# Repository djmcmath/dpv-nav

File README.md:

Tern

Built for Exploration

Welcome to Tern: underwater navigation for technical divers who are tired of getting lost and wondering where they went.

Nominally, this is a simple dead reckoning navigation system designed to be installed on DPVs (aka "scooters").  I'm making this source-available, and attempting to use as many readily-available parts as possible to provide something that'll be accessible to most technical divers.  Some parts of the build are technical -- you'll need to manufacture and solder custom PCBs, flash firmware to ESP32s, and so on, but even if you can't solder or print parts, if you're in the technical diving community, odds are excellent you know someone who can.  

Yes, it's vibe coded.  I used Claude Code to great effect, covering a ton of ground in a matter of months that I hadn't been able to get through on my own.  Say what you will about AI-supported coding, this project exists, and wouldn't without AI support.

About the name:
- It's called Tern, after the Arctic Tern, which is just a fantastic bird.  They navigate from the north pole to the south every year -- mating in the Antarctic, then raising their young in transit and growing to maturity in the Arctic.  Then they migrate BACK to do it all again the next year.  Insane.
- But hey, if a tiny bird can navigate thousands of kilometers every year, perhaps we can build a DIY-capable device that'll allow divers to cover much smaller distances with confidence underwater.

Framing:
- This is NOT "underwater GPS."  GPS doesn't work underwater, and there's no magic that will allow us to violate the laws of physics.  Precise positioning underwater is a delightful engineering problem, and there are a variety of excellent ways to know exactly where you are.  Precision is a function of expense -- how precise your position is depends almost entirely on how much you're willing to spend to get there.
- This *is* a tool that'll tell you much more accurately where you are than anything else readily available in the space at this price point.  If your current process is to read your magnetic compass and keep track of time and distance using your dive computer and mental gymnastics, this will save you a lot of effort and produce a dramatically more accurate result.  I did a dive the other day where my buddy used her wrist-mounted compass -- showing plus or minus 20deg from what I was showing on the DPV -- and, coincidentally, we still hit the wreck.
- The formal name is "dead reckoning," using heading and speed (plus an initial position from GPS on the surface) to determine an "estimated position."  Accuracy of the final position depends on quality of calibration, accuracy of initial position, and time / distance since last fix.  Each iteration takes the previous estimated position, adds the current course and speed, and produces a new estimated position.  Errors, naturally, compound, so the longer it's been since you've actually known where you were, the farther off you may be from where it says you are.  Additionally, knowing EXACTLY where you start matters -- that's why there's external GPS and an indication of fix quality on the headline of the display.
- For planning purposes, assume that the error is about 10% of the distance since your last fix.  So if you submerge and run for 500m, assume you're within 50m of the target.  That'll require dropping a marker and running a reel out to conduct a search to find the wreck.  But at least you have some confidence that you're within a reasonable distance of the right spot.  If you calibrate with care and run a few tests on known courses, you may find that your accuracy is much better.  I've had runs with error rates in the 2-3%, for example.  (Future versions will track heading and speed calibration vs reality to estimate position uncertainty, and will allow reducing uncertainty by crossing known navigation points.)
- Safety note: It's an aid, not an authoritative answer.  Dive within your limits and your training.  Don't blindly follow the computer -- it doesn't know your certification limits or how much breathing gas you have or, frankly, anything about your dive plan.  Heck, it doesn't even know where you are -- it's just estimating.  Additionally, you're adding a device with cables to your DPV, so you're bringing entanglement risk and complexity to your already existing challenges.  So be careful.

Workflow and usage:
- Assemble the whole device
- Flash the firmware to both units (NAV and DISPLAY)
- On the first power-up, the unit will attempt to calibrate gyro and accelerometer.  There will be a series of prompts displayed in the serial monitor walking you through this process.  You should only need to do this once.  Getting it right is important, but it's the least important input to the AHRS algorithm.
- Set up wireless:
-- You can keep it as something that you connect to with a wireless device, or you can set it to automatically connect to a known wireless network.  Calibration is much easier if it has a good full-time wireless connection.
-- Make sure wireless is on ("WiFi AP" in white (or green), not gray, on the display)
-- Connect to wireless AP "Tern," with password "password", then browse to 192.168.4.1.
-- In the "WiFi Networks" section, press "Scan for networks," pick yours off the list, and type the password.  (The page goes quiet for a few seconds during the scan -- the radio has to leave the Tern AP to listen.)  It'll autoconnect to that network at next boot, if it's available.  Then it should appear as "tern.local" on your network.
-- Hidden networks and phone hotspots don't show up in a scan, so type the name in by hand and tick "Hidden network / phone hotspot"; the unit then tries it by name whether or not it's beaconing.  Two things bite people here, both on the phone: the unit is 2.4 GHz only (iPhone: turn on *Personal Hotspot > Maximize Compatibility*; Android: set the hotspot band to 2.4 GHz), and the hotspot has to actually be awake, so leave the Personal Hotspot screen open while pairing.
-- A phone can't serve its own hotspot and stay joined to the Tern AP at the same time.  Save the credentials from the phone first, then leave the page and switch the hotspot on -- the unit picks it up within about a minute on its own.  From a laptop or a second phone, "Try now" next to a saved network forces the attempt immediately.
- Pair the device with the cloud.
-- Create an account on https://map.terndiving.com.
-- In the upper right corner, select the "gear" icon, then "My Devices," then "link a device."
-- On the device, select CONFIG > LINK ACCT.
-- Enter the code from the device into the blank on the web form.  Give it a name.  It's linked now.  You should only have to do this once.
- Perform a baseline calibration.  This requires broad coverage of a "sphere" of directions to provide a baseline for what the magnetic environment of the board and housing look like.  This should happen while the unit is NOT mounted on your scooter, so it should be easy to rotate through the necessary coverage.  You'll need to point the unit in every direction, in every orientation, targeting coverage in roughly 30deg sectors.  So that's "north, level, upright" and "north, level, rolled to left side," and "north, level, rolled to right side," and so on.  A good calibration probably looks like 1200-1500 points, as an entering argument.
- Cal data is automatically uploaded to the cloud, analyzed, and returned.  If you've done ok, you'll have a reasonably low RMS%, and you can hit "Accept."  If it's bad, "Reject" it and try again.
- If it's good-but-not-great, you can run a gap-filling cal.  On tern.local, hit "Check for updates," and it will download a gap-filling target list.  Then run CAL > GAP FILL, pointing the unit at each indicated area.  The main grid gives heading and elevation, with the box in the lower right indicating roll coverage for the selected sector.  Perfection isn't necessary; go at it until you're frustrated, then hit the right button to end and upload the data.
- The cal will be shown on the dive map (Calibration History).  If it's decent, hit "Accept," then, on tern.local, hit "Check for Updates" to install the accepted merged gap-fill calibration data.
- Perform mounted calibration.  We've got a baseline, so we know what the closest parts of the environment look like, now we're figuring out what it looks like with the scooter there.  Similar to the gap-fill cal, you'll get a grid on screen showing coverage, but this is much reduced -- it's all horizontal, just pitched up 30 and down 30, around all the headings.  I find the easiest way to do this is to set the scooter on a stool in my living room.  I pick up one end, resting the other on the stool, and walk slowly around.  Then pick up the other end, walk in a slow circle.  Then level, walk in a slow circle.  I like to arrange the display so I can see it while I'm doing rotations, so I know if I need to go back and spend a little more time in a sector.  As with the other calibrations, it automatically uploads to the cloud, processes, and returns data.  If you can manage less than about 10% RMS on the mounted cal, you're doing ok.
- Before performing the 12-point check, make sure your compass is aligned.  Anecdote: my compass, mounted to my scooter with a neatly milled professional-looking piece of aluminum, turned out to be 8 degrees off.  I've dove with others who've had 15 degree errors.  Please don't assume that your compass is perfect just because it's bolted to your scooter.  The best way to align your compass is to find the magnetic bearing between two points -- for example, your porch and a distant landmark, or the end of a pier and a well known building.  Look up the lat/lon of both points and plug them into any one of the online calculators that provide bearing between two points.  Correct the true bearing to a magnetic bearing, if necessary.  Note that down.  Line up your scooter on that heading and note the error between what your compass says and what you now know to be truth.
- Final heading corrections aka 12-point cal.  It's highly beneficial to provide 12 actual headings to correct final errors.  The unit will prompt you to point at an actual heading (read off the compass, not the Tern DPV-Nav), then press the right button.  When complete, it'll automatically upload and process.  Normally, you'll have one or two sectors that need more coverage.  Check on the dive map to see what they are, and follow the directions (set to RAW bearings, enter the requested indicated headings, process, then "check for updates" to install the improved cal).
- Perform a speed cal.  
-- The design method for an initial cal calls for a 300ft run.  Measure the distance, drag the unit through the water.  The clock automatically starts when it detects flow, and automatically stops when either flow stops or the unit rotates 90 degrees.  The initial thinking was that this had to be done in-water, on a scooter.  But it turns out you can drag it behind a boat, or walk down the beach with the unit duct-taped to a broom stick.  You just need to move it through 300ft of water at a relatively representative speed (30m/min is typical scooter speed).
-- You can also back speed calibration out of a dive that Dive Map has corrected against known positions: that correction reports a speed factor `s` where `true_speed = s x logged_speed`, and since the flow sensor's k-factor is a *divisor*, `k_new = k_old / s`.  Sanity check: if the unit read fast (`s < 1`), k goes up.  Full derivation, the traps, and a worked example are in [docs/dev-calibration-guide.md](docs/dev-calibration-guide.md#deriving-k-from-a-corrected-dive).

On a Dive:
- Plug in the battery, close the housing, make sure the unit boots cleanly
- Let it get a GPS fix on the beach.  GPS doesn't like water at all, so powering everything on and getting this first fix on the beach is better than doing it while the scooter is in the water.
- Use the web page (tern.local) to add named waypoints — go to the Waypoints section and enter a name, latitude, and longitude for each destination you plan to navigate to (e.g. "Bomber Line Start", "MV Scout")
- Once GPS has a solid fix (4 bars, HDOP < 1.0) and you've set waypoints, you can go ahead and put the unit in standby (menu "OFF").  This conserves power, but keeps GPS soft-powered, so it'll reconnect within a few seconds of getting adequate signal.  When you're ready to use it again, press and hold both buttons for about a second (much like a Shearwater).
- Use the menu (**NAV > Select WP**) to scroll through your saved waypoints and select the destination.
- You'll get bearing and range to the waypoint.
- Select CONFIG > LOG:LOW to start logging before the dive.  Preferably, start the logging while you're at the beach so you can get some GPS as an initial entry in the log.  For best results, keep the log running until you're back at the beach with GPS after the dive.
- At intermediate known locations (surface fix, known waypoint), use **NAV > Arrive WP** to snap position and reset accumulated error before the next leg.
- Some tips:
-- Get a fix as close to the target as possible.  e.g. if you can surface transit for a bit, make sure to get 4-bar GPS fix (indicating HDOP < 1.0) before submerging.  
-- Long straight runs at constant speed probably yield best results (need to test to confirm this).  If you're doing a lot of big circles, you're probably losing a little accuracy every time you do it.
-- The unit assumes that if you're moving slowly, you're finning around the wreck and not covering ground.  So if the flow meter is showing <6m/min, it'll assume that heading is meaningless and you're not moving.  This is important if you decide to start finning along for some reason.  Or in other words, it's only really navigating if you're scooting.  If you stop scooting and start finning, the unit assumes you're stopped, and won't update position -- even if you're happily moving through the water.
- When you arrive at the point where the navigator thinks you're at the wreck, you're probably close, but not there.  In Lake Washington, "close" is rarely the same as "close enough."  Plan on putting down a marker (weight, stake in the ground, etc) and running out a reel.  For planning purposes, you're probably within 10% of the total run length (e.g. if it's been 500m since the last fix, total error is probably <50m).  Experience tends to indicate that a 50m radius circle is too big to search all at once, so plan on conducting a spiral search, e.g. let out 5-7m of line, make a circle, let out another 5-7m, etc.

License:
- Tern DPV-Nav is source-available and free for noncommercial use.  Firmware and software are licensed under [PolyForm Noncommercial 1.0.0](LICENSES/PolyForm-Noncommercial-1.0.0.txt); hardware designs and documentation under [CC BY-NC-SA 4.0](LICENSES/CC-BY-NC-SA-4.0.txt).
- Build one, modify it, share your improvements.  Commercial use (selling units or kits, build services, or use in a commercial product) requires a separate license: contact [contact@terndiving.com].
- See [LICENSE.md](LICENSE.md) for which license covers what, [SAFETY.md](SAFETY.md) before you build or dive, and [CONTRIBUTING.md](CONTRIBUTING.md) if you'd like to contribute.

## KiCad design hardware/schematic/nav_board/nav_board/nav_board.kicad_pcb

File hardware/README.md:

Expect this to be:

Schematics: electrical drawings of the board and components, which pins connect to which things

Housing: BOM details, drawings of how the housing and components fit together, STLs for 3D printed parts, etc.

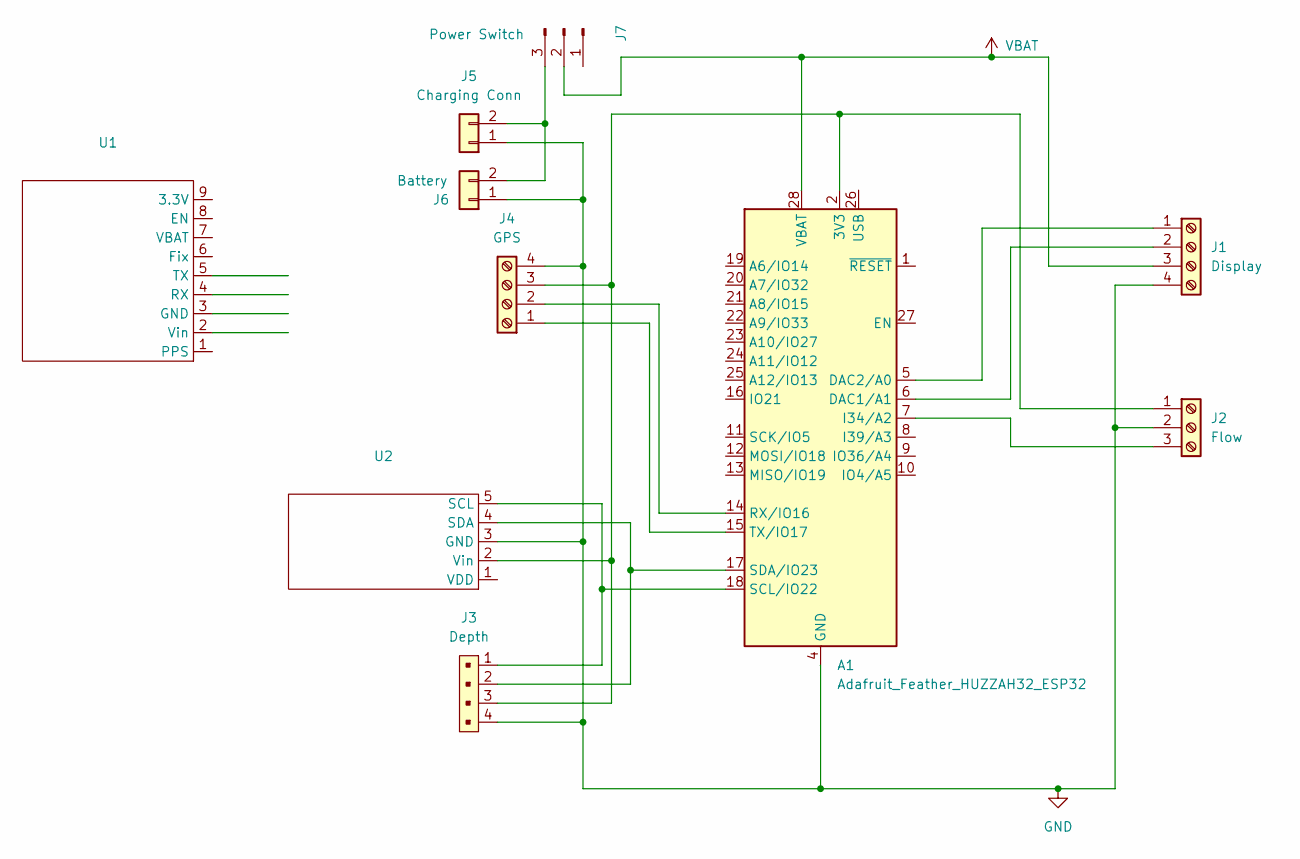
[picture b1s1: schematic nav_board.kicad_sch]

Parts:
A1: Adafruit_Feather_HUZZAH32_ESP32; Adafruit_Feather
J1: Display; Molex_PicoBlade_53047-0410_1x04_P1.25mm_Vertical
J2: Flow; Molex_PicoBlade_53047-0310_1x03_P1.25mm_Vertical
J3: Depth; Molex_PicoBlade_53047-0410_1x04_P1.25mm_Vertical; MPN B4B-XH-A(LF)(SN); Digi-Key_PN 455-2249-ND
J4: GPS; Molex_PicoBlade_53047-0410_1x04_P1.25mm_Vertical
J5: Charging Conn; PinHeader_1x02_P2.54mm_Vertical
J6: Battery; AMASS_XT30U-F_1x02_P5.0mm_Vertical
J7: Power Switch; PinHeader_1x03_P2.54mm_Vertical
U1: Adafruit Ultimate GPS
U2: Pololu Altimu-10 v5

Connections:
GND: A1.4 (GND), J1.4, J2.2, J3.4, J4.4, J5.1, J6.1, U2.3 (GND)
unnamed: A1.2 (3V3), J2.1, J3.3, J4.3, U2.2 (Vin)
unnamed: A1.6 (DAC1/A1), J1.2
unnamed: A1.5 (DAC2/A0), J1.1
unnamed: A1.7 (I34/A2), J2.3
unnamed: A1.14 (RX/IO16), J4.2
unnamed: A1.18 (SCL/IO22), J3.1, U2.5 (SCL)
unnamed: A1.17 (SDA/IO23), J3.2, U2.4 (SDA)
unnamed: A1.15 (TX/IO17), J4.1
unnamed: J5.2, J6.2, J7.3
VBAT: A1.28 (VBAT), J1.3, J7.2

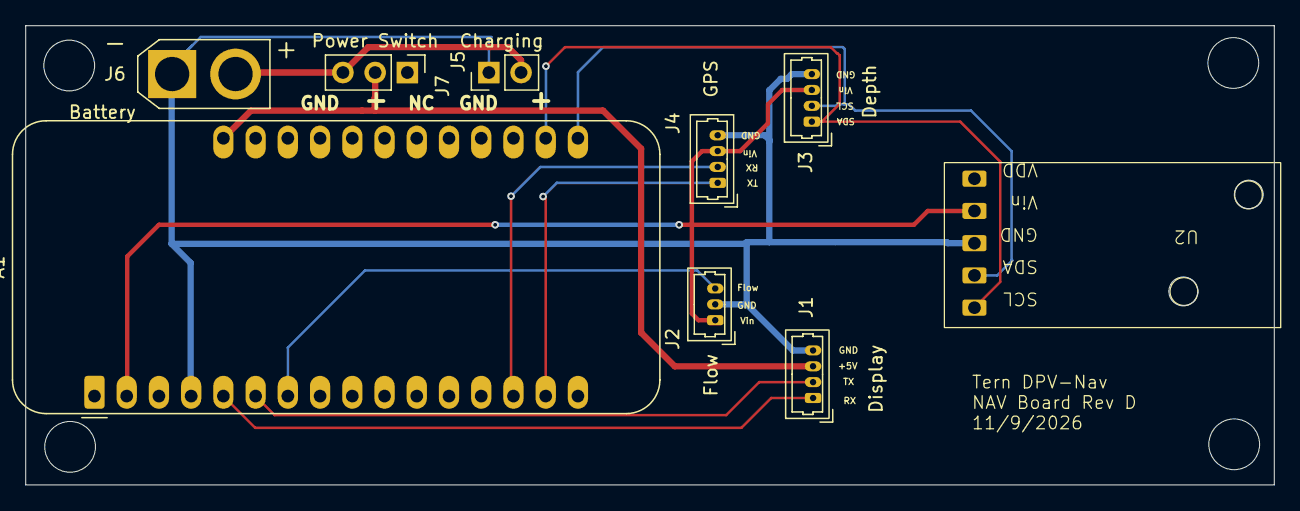
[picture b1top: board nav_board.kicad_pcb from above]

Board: 2 copper layers, 98.4 x 36.2 mm, 9 parts (0 on the bottom side), 11 nets.

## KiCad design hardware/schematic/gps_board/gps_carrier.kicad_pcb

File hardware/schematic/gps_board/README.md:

# Compact GPS carrier — revision B, serial GPS

Open **gps_carrier.kicad_pro** in KiCad 9. The complete Adafruit Ultimate GPS
serial breakout **#746** mounts on the **top** face. The complete QT Py
ESP32-S2 **#5325** mounts on the **bottom** face. The PicoBlade and optional
LED socket are on the QT Py face.

This revision uses `correct_serial_gpsprint.png`. It replaces the USB GPS,
removes tap pads J3, jumper SJ1 and unnecessary diode D2. GPS power and UART
connect through a **nine-pin board-to-board header**. No GPS USB connection,
flying-wire taps or modifications to the GPS module are required.

## Files

- `gps_carrier.kicad_sch`: editable schematic.
- `gps_carrier.kicad_pcb`: **unrouted**, compact opposite-face placement.
- `GPS_Carrier.kicad_sym`, `GPS_Carrier.pretty/`: local libraries.
- `preview/gps_carrier.pdf`: schematic.
- `preview/assembly.png` / `.svg`: top, bottom and side assembly views.
- `preview/placement.pdf`: actual KiCad placement drawing.
- `bom.csv`, `erc.rpt`, `placement-drc.rpt`, `verification.txt`: checks/parts.
- `gps_carrier_rev_A.zip`: superseded historical USB-GPS design.

## Connections

| Connector | Pin | Function |
|---|---:|---|
| J1 Molex 53047-0410 | 1 | Regulated +5 V from main nav |
| J1 | 2 | Ground |
| J1 | 3 | Main-nav TX -> GPS RX |
| J1 | 4 | Main-nav RX <- GPS TX |
| J2 optional 2.54 mm socket | 1 | LED anode (+), through R2 |
| J2 | 2 | LED cathode (-), switched by Q1 |

**J1 pin order remains an assumption**, following the supplied 5V/GND/TX/RX
list; verify against the actual main-nav cable before fabrication. Logic
is 3.3 V; this is not an RS-232 interface.

GPS TX connects directly to J1.4 and, through R1 (4.7 kohm), to QT Py
RX / GPIO16. QT Py TX is unconnected. Main-nav TX connects directly to GPS
RX. QT Py only receives GPS data and controls the indicator.

GPS symbol/footprint numbering follows Adafruit JP1. Viewed from above with
the antenna up and header at the bottom, **pin 1 is the rightmost pin**.

| GPS U1 pin | Printed signal | Carrier connection |
|---:|---|---|
| 1 | PPS | Unconnected |
| 2 | VIN | +5V_NAV |
| 3 | GND | GND |
| 4 | RX | NAV_TX |
| 5 | TX | GPS_TX: nav RX and QT monitor |
| 6 | FIX | Unconnected; firmware evaluates serial fix data |
| 7 | VBAT | Unconnected; use GPS onboard backup-cell holder |
| 8 | EN | Unconnected; GPS onboard pull-up enables receiver |
| 9 | 3.3V | Unconnected regulator output |

## Indicator and power

QT Py A0 / GPIO18 drives Q1 (MMBT3904: 1=B, 2=E, 3=C) through R3 (2.2 kohm).
R4 (100 kohm) holds the LED off during reset. HIGH turns it on. R2 (220 ohm)
limits LED current to approximately 6–14 mA, depending on forward voltage
and supply/diode drop. Choose and test a high-efficiency LED for the desired
visibility; this is for one indicator LED, not a power lamp. J2 is a generic
1x2 female header at 2.54 mm pitch, marked DNP until fitted. No external LED
part number has been selected.

GPS VIN connects directly to NAV 5 V. D1 (SS14) feeds QT Py 5 V and prevents
QT USB power returning to NAV through the power line. QT USB-C remains for
programming. Keep its onboard USB protection jumper in its factory state.
Do not connect the modules' 3.3 V regulator outputs together.

D1 does not isolate UART paths. Power the system together while signals are
active to avoid back-powering an unpowered input. R1 limits monitor-branch
current; it is not a level shifter. Firmware should keep RX as an input,
leave TX unused, disable unnecessary Wi-Fi, and detect stale/missing NMEA
data as well as fix quality. Firmware is not included.

## Mechanical design

- Carrier: **26.400 x 35.290 mm**, two copper layers, nominal 1.6 mm thick.
- GPS: **25.400 x 34.290 mm** CAD envelope, antenna outward, mounted above
  the carrier using a **1x9 header, 2.54 mm pitch**, and two spacers.
- GPS pad centers: X = +10.16 to -10.16 mm (pins 1 to 9), Y = +15.113 mm,
  relative to the centered footprint origin. Header drills: 1.0 mm.
- GPS mounting centers: X = -10.160 / +10.160 mm, Y = -14.605 mm;
  two **2.5 mm NPTH** carrier holes. Select compatible small screws/spacers.
- QT Py: **17.780 x 20.701 mm** PCB envelope, **15.240 mm** between header
  rows, **2.540 mm** pitch. Two 1x7 headers with 1.0 mm carrier drills.
  It is rotated so programming USB faces the carrier's side.
- Supplied QT Py overall size: 21.8 x 17.9 x 5.7 mm. Connector overhang and
  installed cables extend beyond bare PCB envelopes.

**Print/CAD discrepancy:** the supplied GPS print labels height 1.34 in,
bottom-edge-to-mounting-hole distance 1.24 in, and holes 0.09 in. Original
Adafruit v3 CAD gives 1.35 in, 1.25 in and 2.5 mm respectively. This design
uses exact CAD coordinates. Check the actual module before manufacture,
particularly the **0.254 mm vertical mounting difference**. The image alone
does not establish which set matches the physical module. Header pitch,
width and signal order agree.

The ordinary GPS footprint has a full module courtyard. The `_Raised`
variant reserves header/spacer positions while showing the body envelope
on User.Drawings. This permits SMD parts underneath; it does **not** prove
vertical clearance. Select headers/spacers after measuring the GPS battery
holder and installed cell, QT Py underside components, carrier components
and solder joints. Do not mount either module flush. Final stack height and
header/spacer part numbers remain unspecified. Check USB plug, PicoBlade
cable, LED socket and screw-head clearance on the assembled stack.

Assembly-view vertical spacing is illustrative only. There are no module
3D models. GPS antenna faces outward on top. Test acquisition/reception in
the final enclosure with the QT Py and LED operating; RF performance has
not been validated.

## Validation and scope

KiCad 9 parses the schematic, libraries and board. ERC: **zero errors or
warnings**. Placement DRC: **zero placement violations**, with **17 expected
unrouted connections**. `verify_design.py` checks actual PCB pad nets against
KiCad's exported schematic netlist, direct UART connections, QT receive-only
behavior, LED polarity, diode orientation, pitches and schematic association.

The PCB remains **unrouted**, with no fabrication outputs. Before ordering,
verify physical module dimensions and cable pin order, choose mounting
hardware/LED, finish routing and run full DRC.

## Sources and regeneration

Reference CAD, original attribution and licenses are in `reference/`.
`pad-map.json` records source positions; `source-sha256.json` records hashes.

- [Adafruit Ultimate GPS CAD](https://github.com/adafruit/Adafruit-Ultimate-GPS):
  `Adafruit Ultimate GPS.brd` -> `reference/gps-serial.brd`.
- [GPS pinouts](https://learn.adafruit.com/adafruit-ultimate-gps/pinouts).
- [QT Py ESP32-S2 CAD](https://github.com/adafruit/Adafruit-QT-Py-ESP32-S2-PCB):
  `Adafruit QT Py ESP32-S2.brd` -> `reference/qtpy-s2.brd`.
- [QT Py pinouts](https://learn.adafruit.com/adafruit-qt-py-esp32-s2/pinouts).

Adafruit designs: Limor Fried/Ladyada for Adafruit Industries. Preserve
original attribution and Creative Commons Share-Alike terms supplied in
reference files when redistributing derivative geometry. Standard KiCad
components retain their CC-BY-SA 4.0 library-exception terms and standard
3D model links. Historical USB CAD is retained only for provenance.

Regenerate with `build_libraries.py`, `build_schematic.py`, `build_pcb.py`
and `build_assembly_view.py`. Use KiCad's bundled Python for `build_pcb.py`
and `verify_design.py`. These overwrite generated files; preserve manual
changes first.

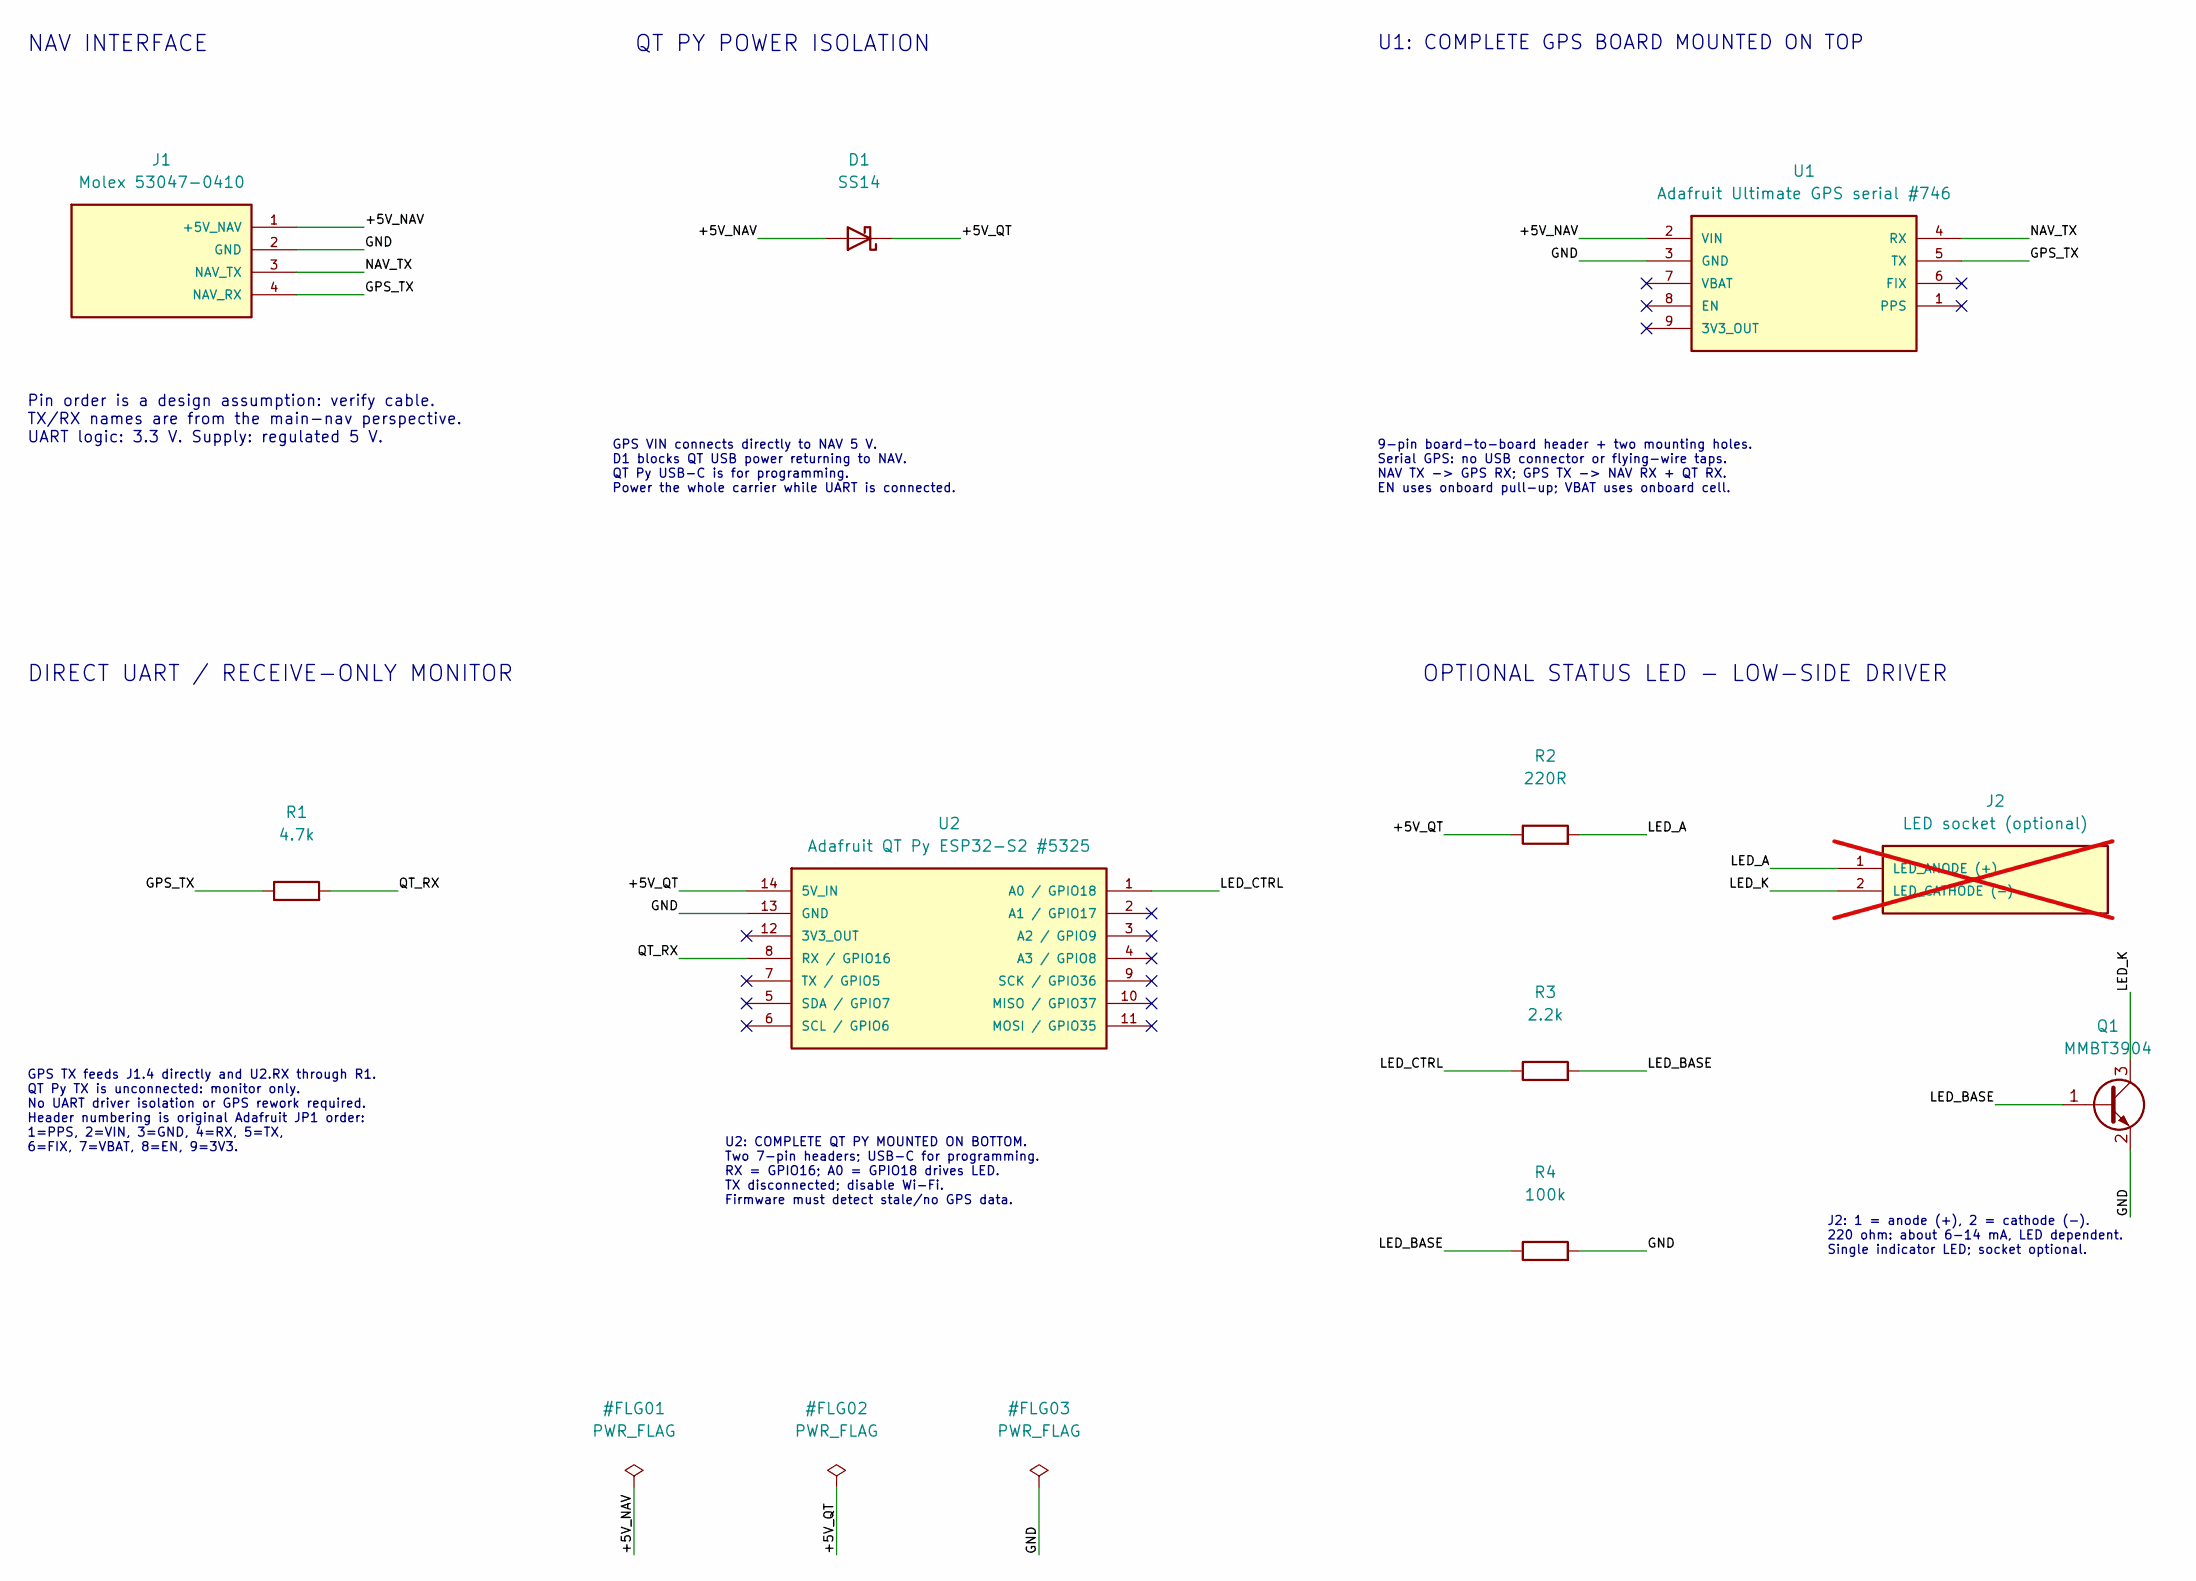
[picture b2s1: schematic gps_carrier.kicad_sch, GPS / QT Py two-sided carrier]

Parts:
D1: SS14; D_SOD-123
J1: Molex 53047-0410; Molex_PicoBlade_53047-0410_1x04_P1.25mm_Vertical
J2: LED socket (optional); PinSocket_1x02_P2.54mm_Vertical; not fitted
Q1: MMBT3904; SOT-23
R1: 4.7k; R_0603_1608Metric
R2: 220R; R_0603_1608Metric
R3: 2.2k; R_0603_1608Metric
R4: 100k; R_0603_1608Metric
U1: Adafruit Ultimate GPS serial #746; Adafruit_Ultimate_GPS_Serial_746_THT_Raised
U2: Adafruit QT Py ESP32-S2 #5325; Adafruit_QT_Py_ESP32_S2_THT

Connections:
/+5V_NAV: D1.2 (A), J1.1 (+5V_NAV), U1.2 (VIN)
/+5V_QT: D1.1 (K), R2.1, U2.14 (5V_IN)
/GND: J1.2 (GND), Q1.2 (E), R4.2, U1.3 (GND), U2.13 (GND)
/GPS_TX: J1.4 (NAV_RX), R1.1, U1.5 (TX)
/LED_A: J2.1 (LED_ANODE (+)), R2.2
/LED_BASE: Q1.1 (B), R3.2, R4.1
/LED_CTRL: R3.1, U2.1 (A0 / GPIO18)
/LED_K: J2.2 (LED_CATHODE (-)), Q1.3 (C)
/NAV_TX: J1.3 (NAV_TX), U1.4 (RX)
/QT_RX: R1.2, U2.8 (RX / GPIO16)

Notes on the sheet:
NAV INTERFACE
Pin order is a design assumption: verify cable. TX/RX names are from the main-nav perspective. UART logic: 3.3 V. Supply: regulated 5 V.
QT PY POWER ISOLATION
GPS VIN connects directly to NAV 5 V. D1 blocks QT USB power returning to NAV. QT Py USB-C is for programming. Power the whole carrier while UART is connected.
U1: COMPLETE GPS BOARD MOUNTED ON TOP
9-pin board-to-board header + two mounting holes. Serial GPS: no USB connector or flying-wire taps. NAV TX -> GPS RX; GPS TX -> NAV RX + QT RX. EN uses onboard pull-up; VBAT uses onboard cell.
DIRECT UART / RECEIVE-ONLY MONITOR
GPS TX feeds J1.4 directly and U2.RX through R1. QT Py TX is unconnected: monitor only. No UART driver isolation or GPS rework required. Header numbering is original Adafruit JP1 order: 1=PPS, 2=VIN, 3=GND, 4=RX, 5=TX, 6=FIX, 7=VBAT, 8=EN, 9=3V3.
U2: COMPLETE QT PY MOUNTED ON BOTTOM. Two 7-pin headers; USB-C for programming. RX = GPIO16; A0 = GPIO18 drives LED. TX disconnected; disable Wi-Fi. Firmware must detect stale/no GPS data.
OPTIONAL STATUS LED - LOW-SIDE DRIVER
J2: 1 = anode (+), 2 = cathode (-). 220 ohm: about 6-14 mA, LED dependent. Single indicator LED; socket optional.

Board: 2 copper layers, 10 parts (3 on the bottom side), 10 nets, no tracks yet.

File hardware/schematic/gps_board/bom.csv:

Reference,Value,Footprint,Populate,Notes
J1,Molex 53047-0410,GPS_Carrier:Molex_PicoBlade_53047-0410_1x04_P1.25mm_Vertical,Yes,
D1,SS14,GPS_Carrier:D_SOD-123,Yes,
U1,Adafruit Ultimate GPS serial #746,GPS_Carrier:Adafruit_Ultimate_GPS_Serial_746_THT_Raised,Yes,Serial #746 mounted on top with 1x9 header and two spacers
R1,4.7k,GPS_Carrier:R_0603_1608Metric,Yes,
U2,Adafruit QT Py ESP32-S2 #5325,GPS_Carrier:Adafruit_QT_Py_ESP32_S2_THT,Yes,Mounted on bottom with two 1x7 headers; underside clearance required
R2,220R,GPS_Carrier:R_0603_1608Metric,Yes,
J2,LED socket (optional),GPS_Carrier:PinSocket_1x02_P2.54mm_Vertical,Optional,Optional external LED socket; LED part unspecified
R3,2.2k,GPS_Carrier:R_0603_1608Metric,Yes,
Q1,MMBT3904,GPS_Carrier:SOT-23,Yes,
R4,100k,GPS_Carrier:R_0603_1608Metric,Yes,

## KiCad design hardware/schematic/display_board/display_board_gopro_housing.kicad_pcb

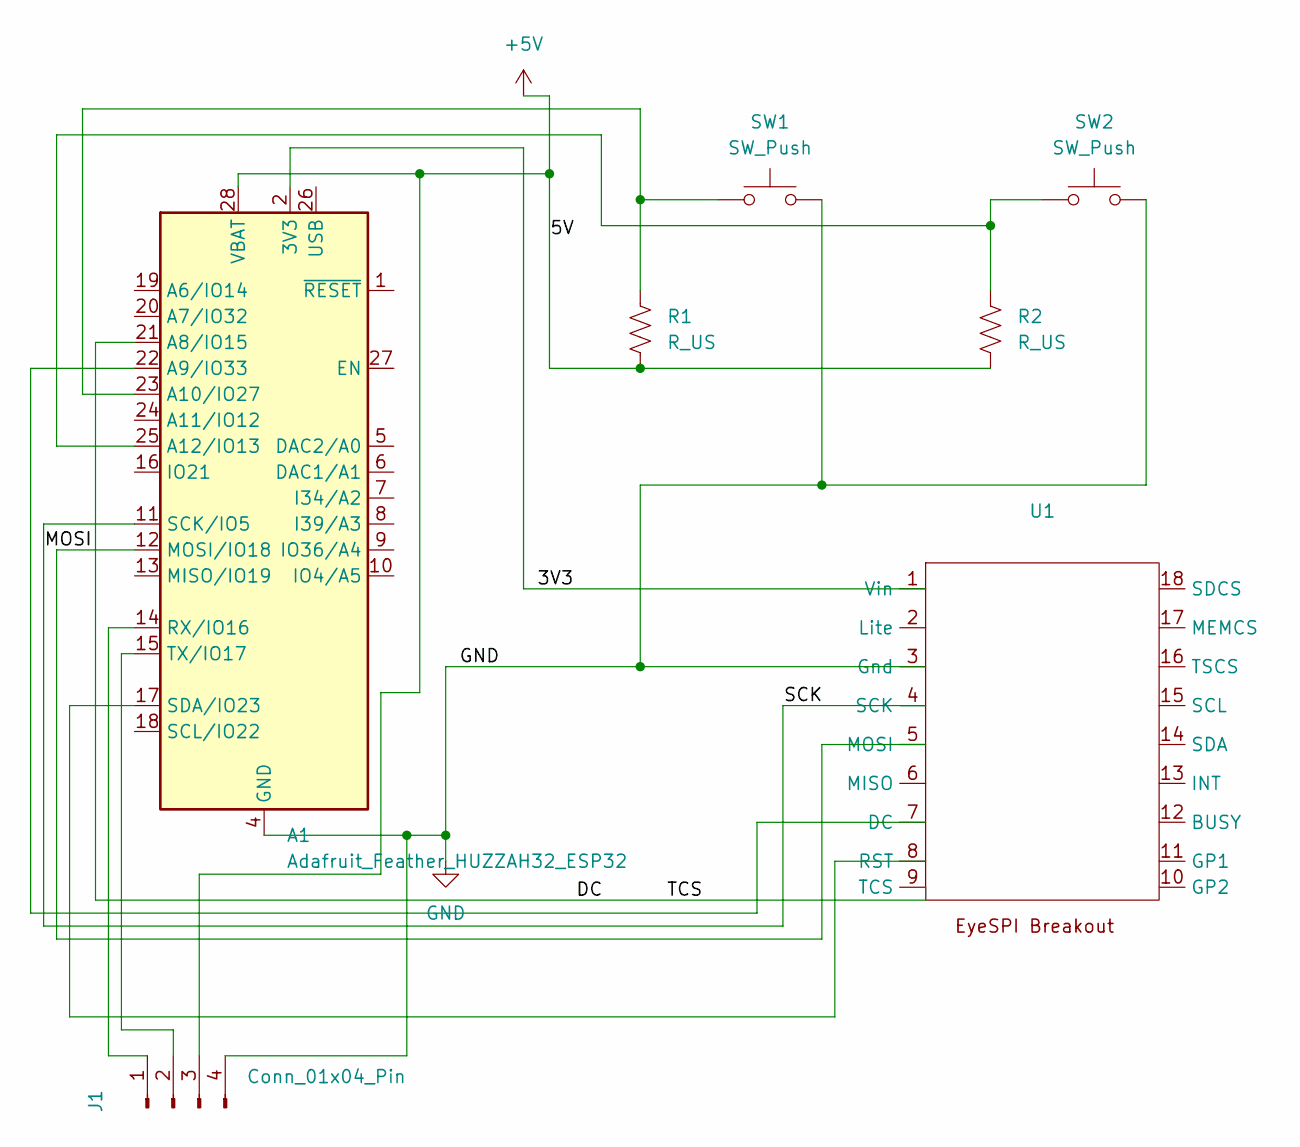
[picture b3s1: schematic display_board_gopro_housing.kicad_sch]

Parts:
A1: Adafruit_Feather_HUZZAH32_ESP32; Adafruit_Feather
J1: Conn_01x04_Pin; Molex_PicoBlade_53047-0410_1x04_P1.25mm_Vertical
R1, R2: R_US; R_Axial_DIN0207_L6.3mm_D2.5mm_P7.62mm_Horizontal
SW1, SW2: SW_Push; Molex_PicoBlade_53047-0210_1x02_P1.25mm_Vertical
U1: EyeSPI_Breakout

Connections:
+5V: A1.28 (VBAT), J1.3, R1.2, R2.2
/3V3: A1.2 (3V3), U1.1 (Vin)
/DC: A1.21 (A8/IO15), U1.9 (TCS)
/MOSI: A1.11 (SCK/IO5), U1.4 (SCK)
GND: A1.4 (GND), J1.4, SW1.2, SW2.2, U1.3 (Gnd)
unnamed: A1.22 (A9/IO33), U1.7 (DC)
unnamed: A1.23 (A10/IO27), R1.1, SW1.1
unnamed: A1.25 (A12/IO13), R2.1, SW2.1
unnamed: A1.12 (MOSI/IO18), U1.5 (MOSI)
unnamed: A1.14 (RX/IO16), J1.1
unnamed: A1.17 (SDA/IO23), U1.8 (RST)
unnamed: A1.15 (TX/IO17), J1.2

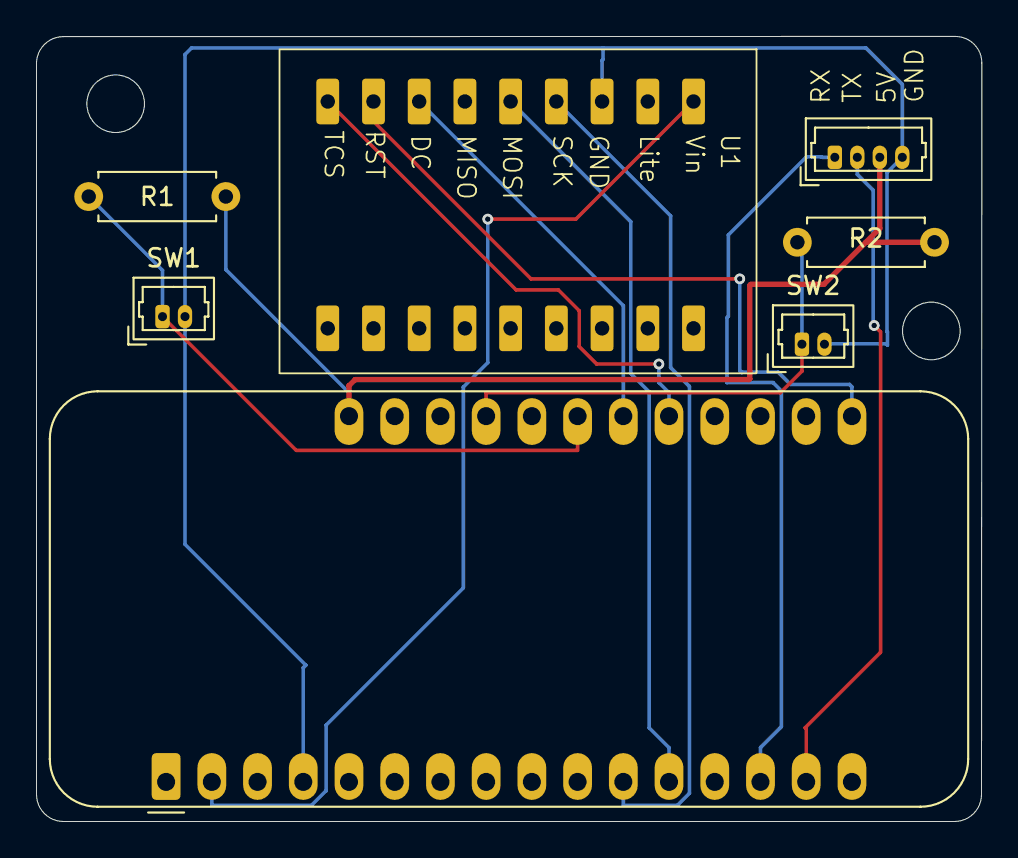
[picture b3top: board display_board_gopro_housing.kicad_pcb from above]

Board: 2 copper layers, 52.5 x 43.6 mm, 7 parts (0 on the bottom side), 12 nets.

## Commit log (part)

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2025-12-21 updating readme
2026-01-17 Numerous changes; working towards first real build
2026-01-18 Setting up intellisense
2026-02-15 First version where AHRS heading actually tracks!
2026-03-04 Stable heading
2026-03-04 Adding docs to make sure we don't break heading again
2026-03-10 Starting in on board design
2026-03-10 Adding lat/lon to logging
2026-03-10 First draft of display PCB
2026-03-10 Updating board project
2026-03-10 updating pcb
2026-03-11 updating pcb again
2026-03-13 Working calibration efforts
2026-03-14 Running calibration work
2026-03-14 another cal run
2026-03-14 updated mag_cal
2026-03-15 updated mag_cal.json
2026-03-15 Updating docs for new realities
2026-03-15 Added NVS state restoration and reduced frequency of logging at low level.
2026-03-18 Tweaking board-pins
2026-03-19 First version of Nav PCB
2026-03-20 Added speed calibration (first effort)
2026-03-20 First order of PCBs
2026-04-10 Collection of display improvements
2026-04-11 Updating cal routine
2026-04-16 Added improved wireless control - now it joins a known wireless station, which is helpful in the dive locker. Added two-button turn-on (and low power mode) Improved GPS performance with hot-start Red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
2026-05-15 Updating cal process to add 12-point Fourier fit of actual data as a final step.
2026-05-15 mostly just cal data
2026-05-15 Correcting bug in Fourier fit Adding reload button to web page
2026-05-15 Fixing small bug in naming
2026-05-17 Fixed bug where the speed calibration wasn't being loaded at boot. Created scripts to adjust reconstruction data post dive
2026-05-18 Adjust log level and default network login
2026-05-18 Updating logging interval for LOW to 1sec
2026-06-02 Updating python scripts and docs for ingesting data logs
2026-06-03 Revise README for Tern navigation system
    Updated the README to enhance clarity and provide additional details on the Tern navigation system's features and usage instructions.
2026-06-04 Updating nav board, and also K-factor for speed cal
2026-06-05 Added multiple named waypoints
2026-06-12 Adding a logo to the images folder. Updating python tool to correct for a calibration run, e.g. reciprocal legs between two known points. Adding GPS fix quality to LOW log level.
2026-06-12 Fixing a merge correction to deconflict a variable that had been named differently between branchs.
2026-06-13 Improving GPS indication
2026-06-15 Adding logo to boot screen, updating speed cal, improving the web UI.
